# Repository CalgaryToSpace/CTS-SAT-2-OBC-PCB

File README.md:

# CTS-SAT-2-OBC-PCB

This is the design repository for the CTS-SAT-2 onboard computer (OBC) PCB.

This OBC is host to an STM32 and several flash chips, and interfaces with all other electrical components on the 3U CubeSat.

## Repository Contents

* OBC PCB (KiCad; in progress) 
* STM32CubeIDE Pinout/IOC configuration (not yet done)

## Contributors

* Nadeem M ([DeemDeem52](https://github.com/DeemDeem52))
* Others

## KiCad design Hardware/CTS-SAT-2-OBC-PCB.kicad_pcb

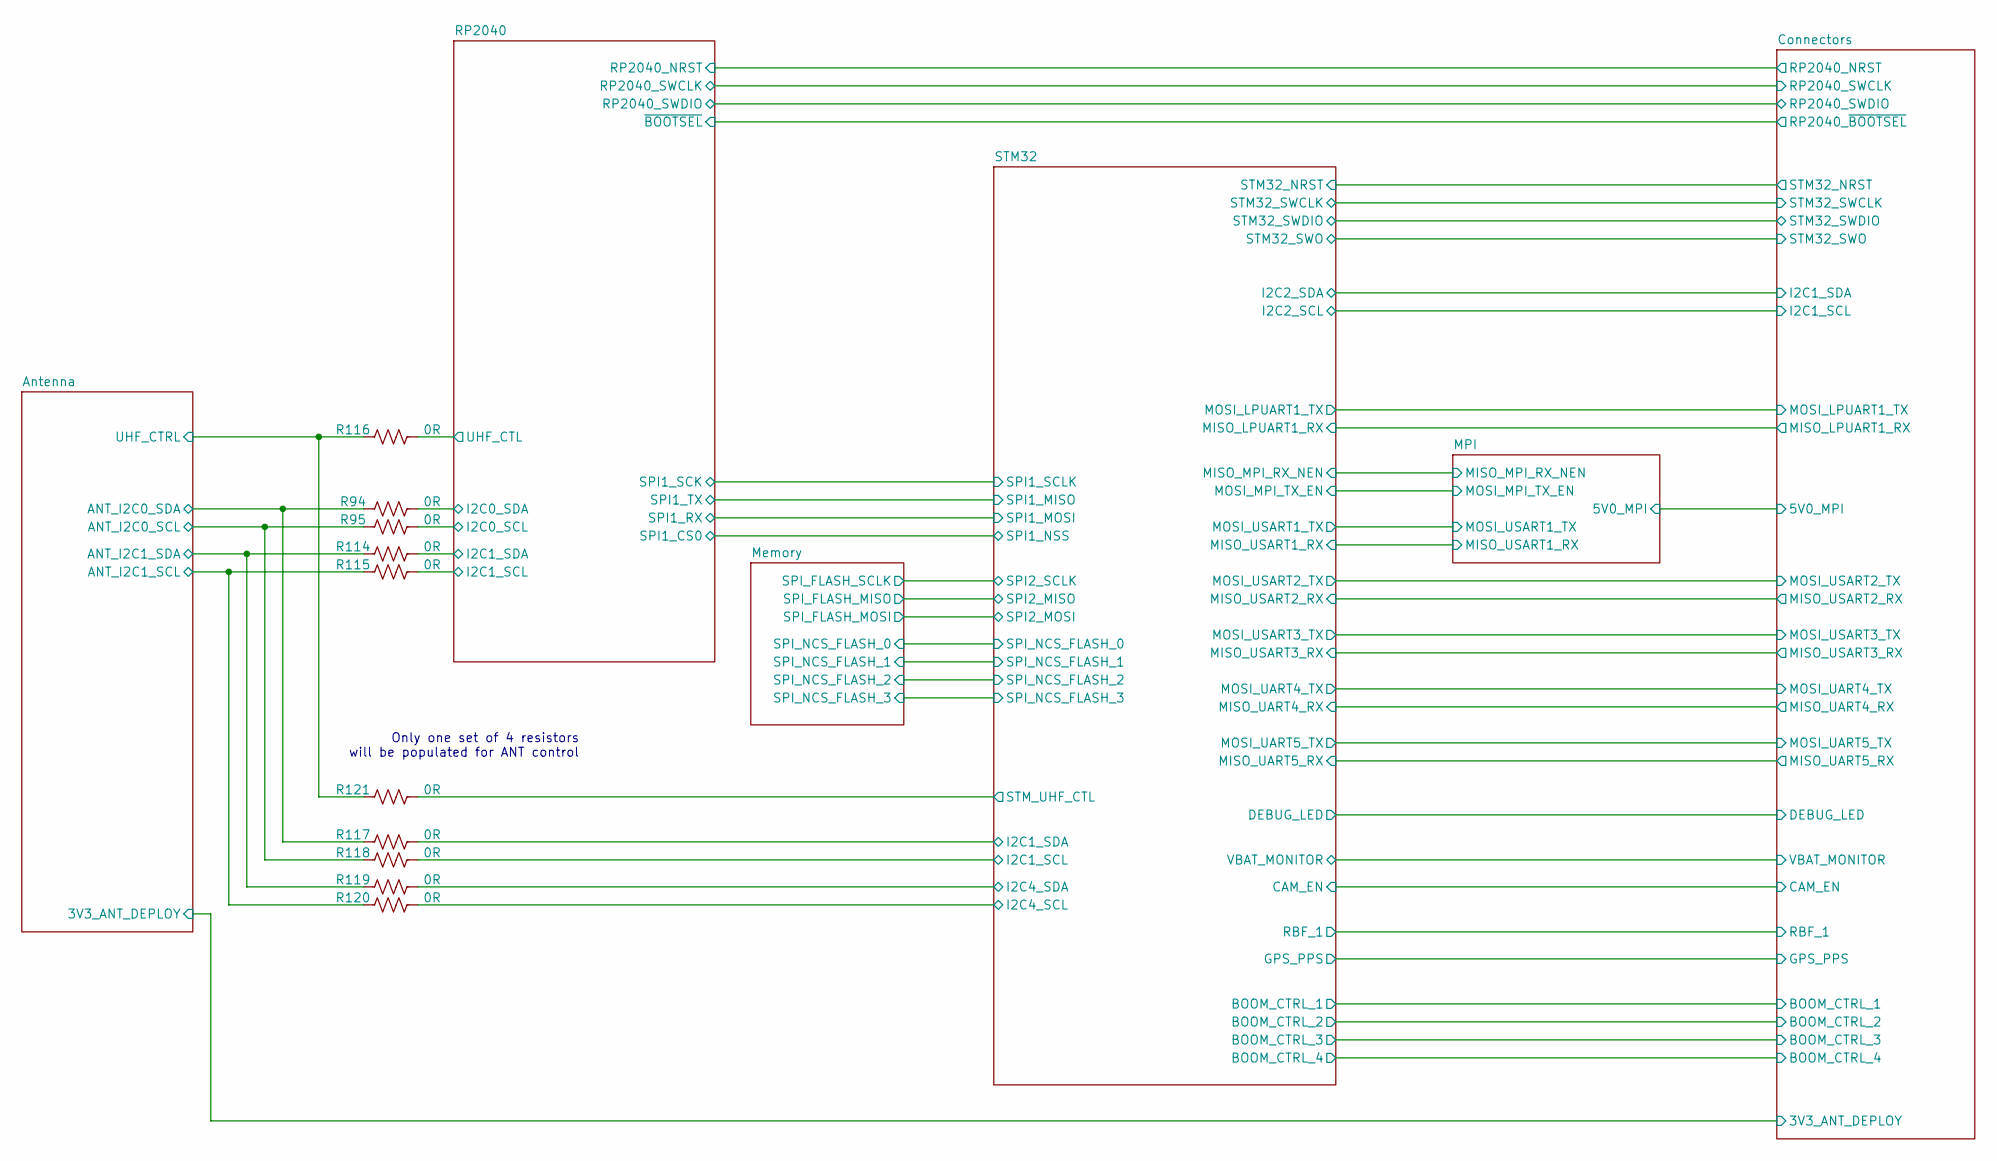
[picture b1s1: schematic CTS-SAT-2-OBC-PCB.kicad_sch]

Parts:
R94, R95, R114, R115, R116, R117, R118, R119, R120, R121: 0R; R_0603_1608Metric

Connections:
/Antenna/ANT_I2C0_SCL: R95.1, R118.1; also elsewhere on the board
/Antenna/ANT_I2C0_SDA: R94.1, R117.1; also elsewhere on the board
/Antenna/ANT_I2C1_SCL: R115.1, R120.1; also elsewhere on the board
/Antenna/ANT_I2C1_SDA: R114.1, R119.1; also elsewhere on the board
/Antenna/UHF_CTRL: R116.1, R121.1; also elsewhere on the board
/RP2040/I2C0_SCL: R95.2; also elsewhere on the board
/RP2040/I2C0_SDA: R94.2; also elsewhere on the board
/RP2040/I2C1_SCL: R115.2; also elsewhere on the board
/RP2040/I2C1_SDA: R114.2; also elsewhere on the board
/RP2040/UHF_CTL: R116.2; also elsewhere on the board
/STM32/I2C1_SCL: R118.2; also elsewhere on the board
/STM32/I2C1_SDA: R117.2; also elsewhere on the board
/STM32/I2C4_SCL: R120.2; also elsewhere on the board
/STM32/I2C4_SDA: R119.2; also elsewhere on the board
/STM32/STM_UHF_CTL: R121.2

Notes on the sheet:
Only one set of 4 resistors will be populated for ANT control

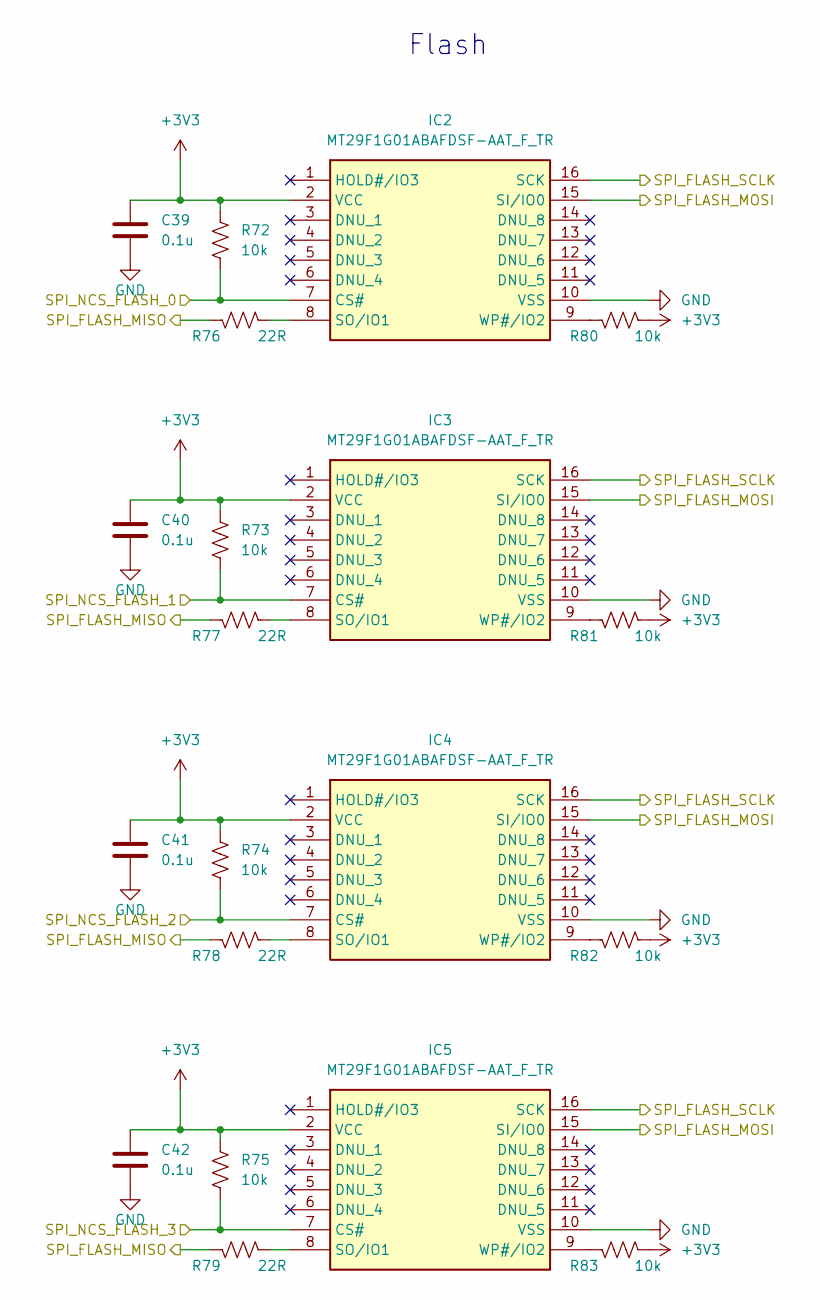
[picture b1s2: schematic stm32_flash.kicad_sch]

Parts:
C39, C40, C41, C42: 0.1u; C_0603_1608Metric
IC2, IC3, IC4, IC5: MT29F1G01ABAFDSF-AAT_F_TR; SOIC-16W_7.5x10.3mm_P1.27mm; Mouser Part Number 340-312330-REEL
R72, R73, R74, R75, R80, R81, R82, R83: 10k; R_0603_1608Metric
R76, R77, R78, R79: 22R; R_0603_1608Metric

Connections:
+3V3: C39.2, C40.2, C41.2, C42.2, IC2.2 (VCC), IC3.2 (VCC), IC4.2 (VCC), IC5.2 (VCC), R72.1, R73.1, R74.1, R75.1, R80.2, R81.2, R82.2, R83.2; also elsewhere on the board
/Memory/SPI_FLASH_MISO: R76.2, R77.2, R78.2, R79.2; also elsewhere on the board
/Memory/SPI_FLASH_MOSI: IC2.15 (SI/IO0), IC3.15 (SI/IO0), IC4.15 (SI/IO0), IC5.15 (SI/IO0); also elsewhere on the board
/Memory/SPI_FLASH_SCLK: IC2.16 (SCK), IC3.16 (SCK), IC4.16 (SCK), IC5.16 (SCK); also elsewhere on the board
/Memory/SPI_NCS_FLASH_0: IC2.7 (CS#), R72.2; also elsewhere on the board
/Memory/SPI_NCS_FLASH_1: IC3.7 (CS#), R73.2; also elsewhere on the board
/Memory/SPI_NCS_FLASH_2: IC4.7 (CS#), R74.2; also elsewhere on the board
/Memory/SPI_NCS_FLASH_3: IC5.7 (CS#), R75.2; also elsewhere on the board
GND: C39.1, C40.1, C41.1, C42.1, IC2.10 (VSS), IC3.10 (VSS), IC4.10 (VSS), IC5.10 (VSS); also elsewhere on the board
unnamed: IC2.8 (SO/IO1), R76.1
unnamed: IC2.9 (WP#/IO2), R80.1
unnamed: IC3.8 (SO/IO1), R77.1
unnamed: IC3.9 (WP#/IO2), R81.1
unnamed: IC4.8 (SO/IO1), R78.1
unnamed: IC4.9 (WP#/IO2), R82.1
unnamed: IC5.8 (SO/IO1), R79.1
unnamed: IC5.9 (WP#/IO2), R83.1

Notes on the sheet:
Flash

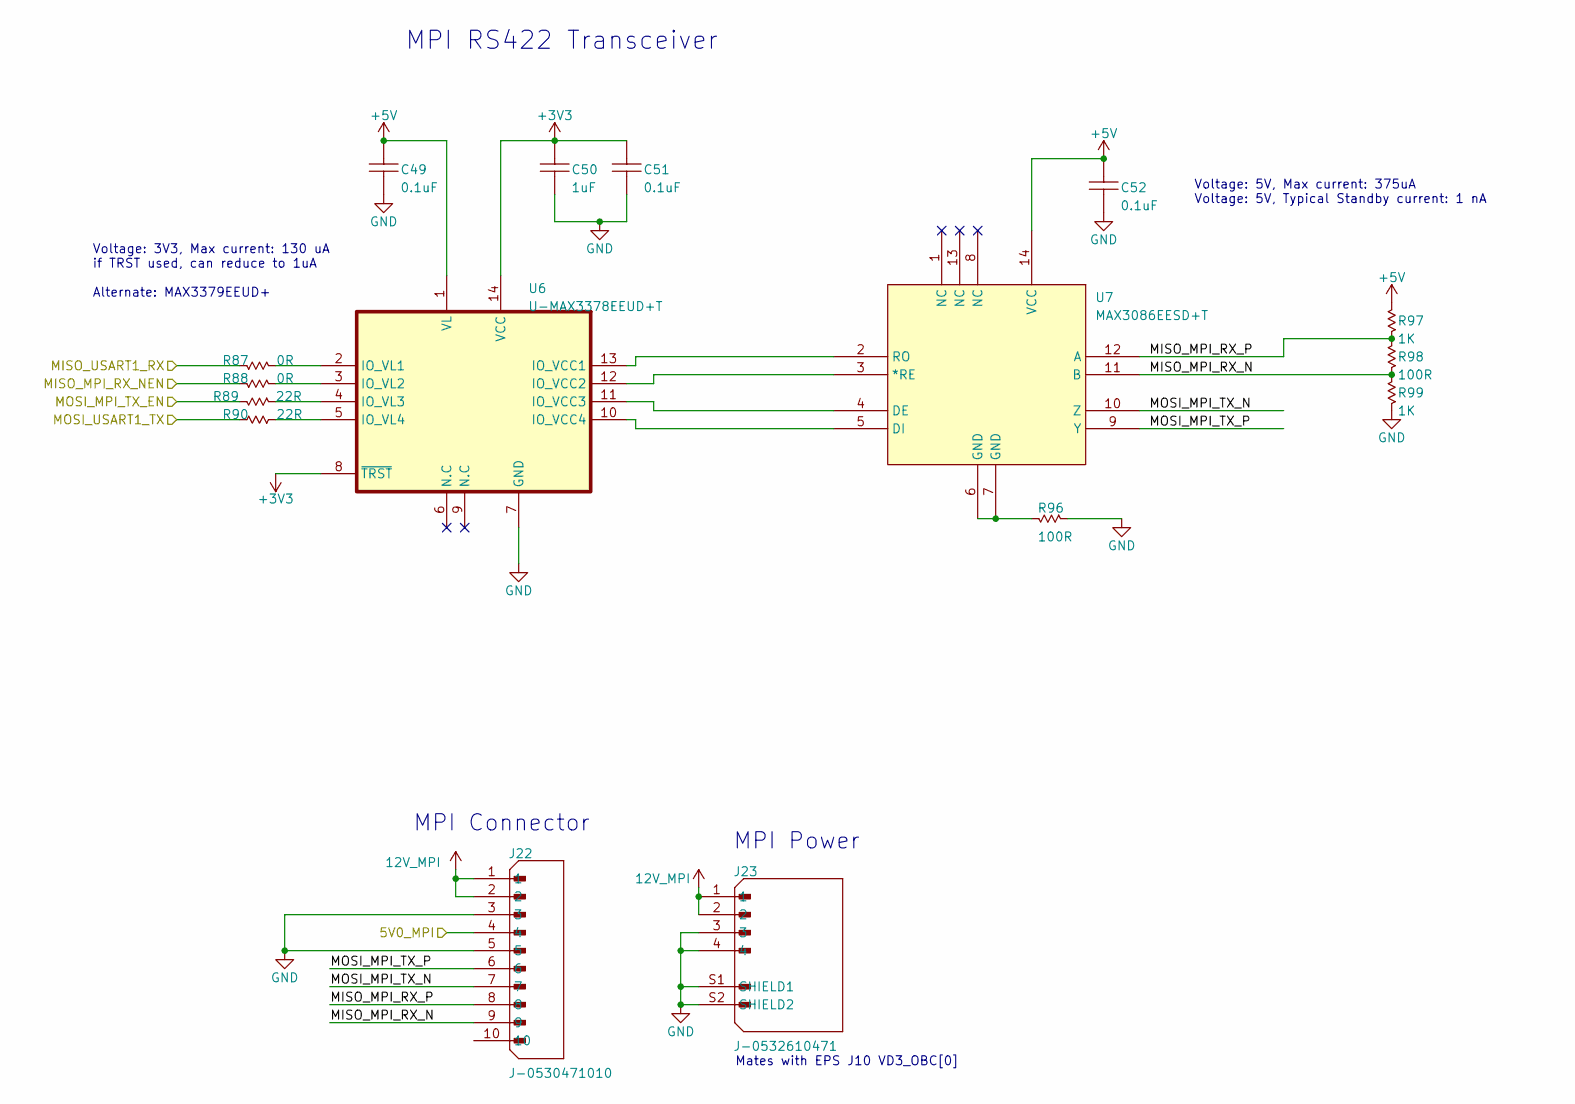
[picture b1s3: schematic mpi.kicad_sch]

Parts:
C49, C51, C52: 0.1uF; C_0603_1608Metric; RATED VOLTAGE 25; MANUFACTURER PART # GCJ188R71E104KA12D
C50: 1uF; C_0603_1608Metric; MANUFACTURER PART # CC0603KRX7R8BB105
J22: J-0530471010; MANUFACTURER PART # 0530471010
J23: J-0532610471; J-53261-0471; MANFACTURER PART # 0532610471
R87, R88: 0R; R_0603_1608Metric; MANUFACTURER PART # RMCF0603ZT0R00
R89, R90: 22R; R_0603_1608Metric; MANUFACTURER PART # RR0816Q-220-D
R96, R98: 100R; R_0603_1608Metric; MANUFACTURER PART # RR08P100DCT-ND
R97, R99: 1K; R_0603_1608Metric; MANUFACTURER PART # CPF0603F1K0C1
U6: U-MAX3378EEUD+T; MANUFACTURER PART # MAX3378EEUD+T; LCSC PART # C143441
U7: MAX3086EESD+T; U-MAX3086EESD+T; MANUFACTURER PART # MAX3086EESD+T; LCSC PART # C2671104

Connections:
12V_MPI: J22.1, J22.2, J23.1, J23.2
+3V3: C50.2, C51.1, U6.8 (~TRST), U6.14 (VCC); also elsewhere on the board
+5V: C49.1, C52.1, R97.2, U6.1 (VL), U7.14 (VCC); also elsewhere on the board
/Connectors/5V0_MPI: J22.4; also elsewhere on the board
/MPI/MISO_MPI_RX_N: J22.9, R98.1, R99.2, U7.11 (B)
/MPI/MISO_MPI_RX_NEN: R88.1; also elsewhere on the board
/MPI/MISO_MPI_RX_P: J22.8, R97.1, R98.2, U7.12 (A)
/MPI/MISO_USART1_RX: R87.1; also elsewhere on the board
/MPI/MOSI_MPI_TX_EN: R89.2; also elsewhere on the board
/MPI/MOSI_MPI_TX_N: J22.7, U7.10 (Z)
/MPI/MOSI_MPI_TX_P: J22.6, U7.9 (Y)
/MPI/MOSI_USART1_TX: R90.2; also elsewhere on the board
GND: C49.2, C50.1, C51.2, C52.2, J22.3, J22.5, J23.3, J23.4, J23.S1 (SHIELD1), J23.S2 (SHIELD2), R96.1, R99.1, U6.7 (GND); also elsewhere on the board
unnamed: R96.2, U7.6 (GND), U7.7 (GND)
unnamed: U6.13 (IO_VCC1), U7.2 (RO)
unnamed: U6.12 (IO_VCC2), U7.3 (*RE)
unnamed: U6.11 (IO_VCC3), U7.4 (DE)
unnamed: U6.10 (IO_VCC4), U7.5 (DI)
unnamed: R87.2, U6.2 (IO_VL1)
unnamed: R88.2, U6.3 (IO_VL2)
unnamed: R89.1, U6.4 (IO_VL3)
unnamed: R90.1, U6.5 (IO_VL4)

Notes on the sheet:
Voltage: 3V3, Max current: 130 uA if TRST used, can reduce to 1uA Alternate: MAX3379EEUD+
Voltage: 5V, Max current: 375uA Voltage: 5V, Typical Standby current: 1 nA
Mates with EPS J10 VD3_OBC[0]
MPI Connector
MPI Power
MPI RS422 Transceiver

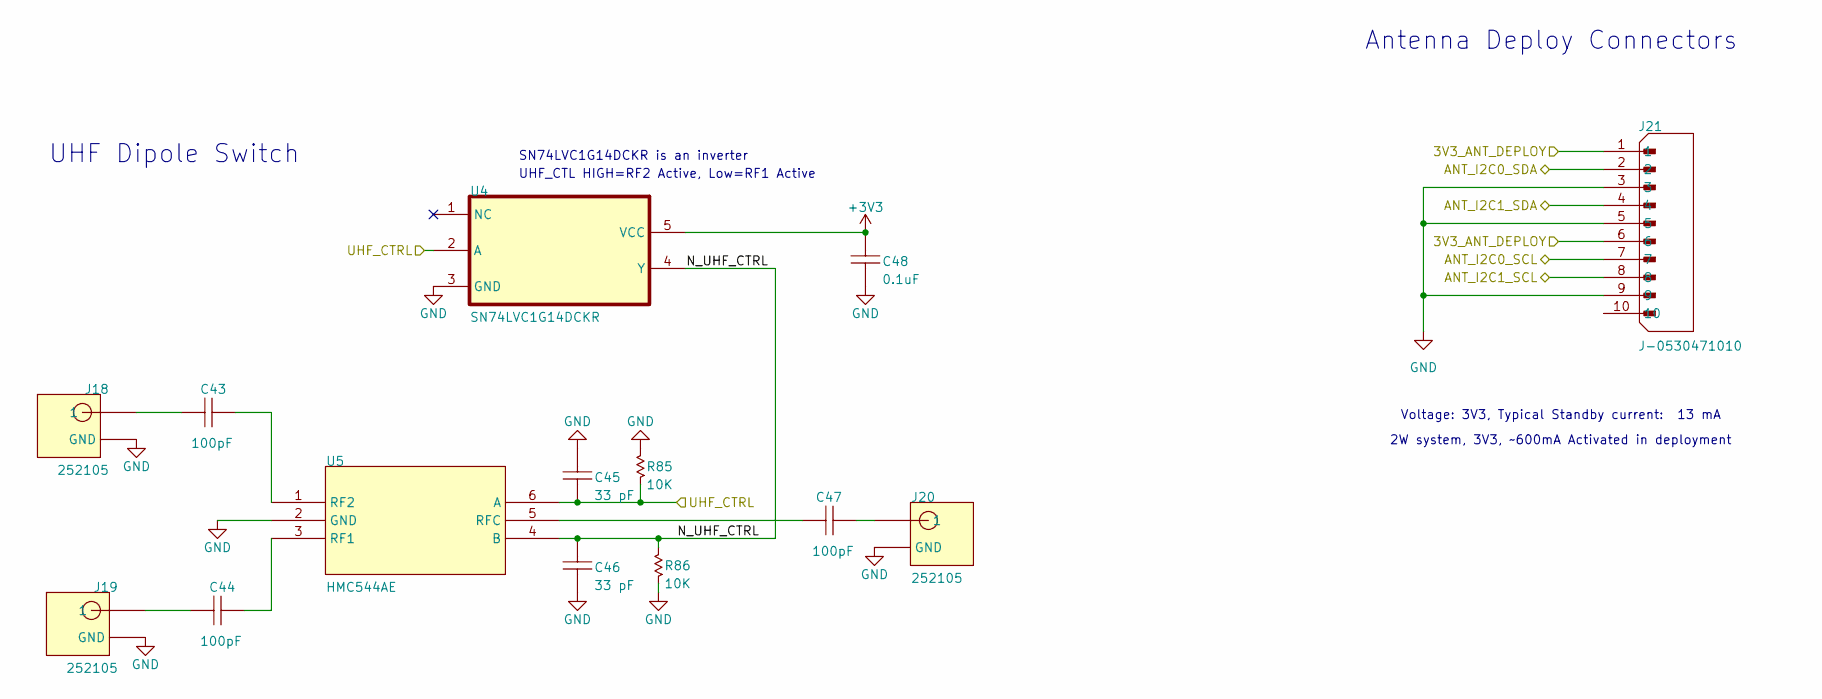
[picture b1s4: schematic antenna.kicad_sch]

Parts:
C43, C44, C47: 100pF; C_0603_1608Metric; MANUFACTURER PART # CC0603KRX7R9BB101
C45, C46: 33 pF; C_0603_1608Metric; MANUFACTURER PART # C0603C330K5RAC7867
C48: 0.1uF; C_0603_1608Metric; RATED VOLTAGE 25; MANUFACTURER PART # GCJ188R71E104KA12D
J18, J19, J20: 252105; J-252105; MANUFACTURER PART # 252105
J21: J-0530471010; MANUFACTURER PART # 0530471010
R85, R86: 10K; R_0603_1608Metric; MANUFACTURER PART # CPF0603B10KE
U4: SN74LVC1G14DCKR; U-SN74LVC1G14DCKR; MANUFACTURER PART # SN74LVC1G14DCKR; LCSC PART # C35740
U5: HMC544AE; U-HMC544AETR; MANUFACTURER PART # HMC544AETR; LCSC PART # C579555

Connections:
+3V3: C48.2, U4.5 (VCC); also elsewhere on the board
/Antenna/3V3_ANT_DEPLOY: J21.1, J21.6; also elsewhere on the board
/Antenna/ANT_I2C0_SCL: J21.7; also elsewhere on the board
/Antenna/ANT_I2C0_SDA: J21.2; also elsewhere on the board
/Antenna/ANT_I2C1_SCL: J21.8; also elsewhere on the board
/Antenna/ANT_I2C1_SDA: J21.4; also elsewhere on the board
/Antenna/N_UHF_CTRL: C46.2, R86.2, U4.4 (Y), U5.4 (B)
/Antenna/UHF_CTRL: C45.1, R85.1, U4.2 (A), U5.6 (A); also elsewhere on the board
GND: C45.2, C46.1, C48.1, J18.0 (GND), J19.0 (GND), J20.0 (GND), J21.3, J21.5, J21.9, R85.2, R86.1, U4.3 (GND), U5.2 (GND); also elsewhere on the board
unnamed: C43.1, J18.1
unnamed: C44.1, J19.1
unnamed: C47.2, J20.1
unnamed: C44.2, U5.3 (RF1)
unnamed: C43.2, U5.1 (RF2)
unnamed: C47.1, U5.5 (RFC)

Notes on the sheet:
Antenna Deploy Connectors
Voltage: 3V3, Typical Standby current: 13 mA
SN74LVC1G14DCKR is an inverter
UHF Dipole Switch
UHF_CTL HIGH=RF2 Active, Low=RF1 Active
2W system, 3V3, ~600mA Activated in deployment

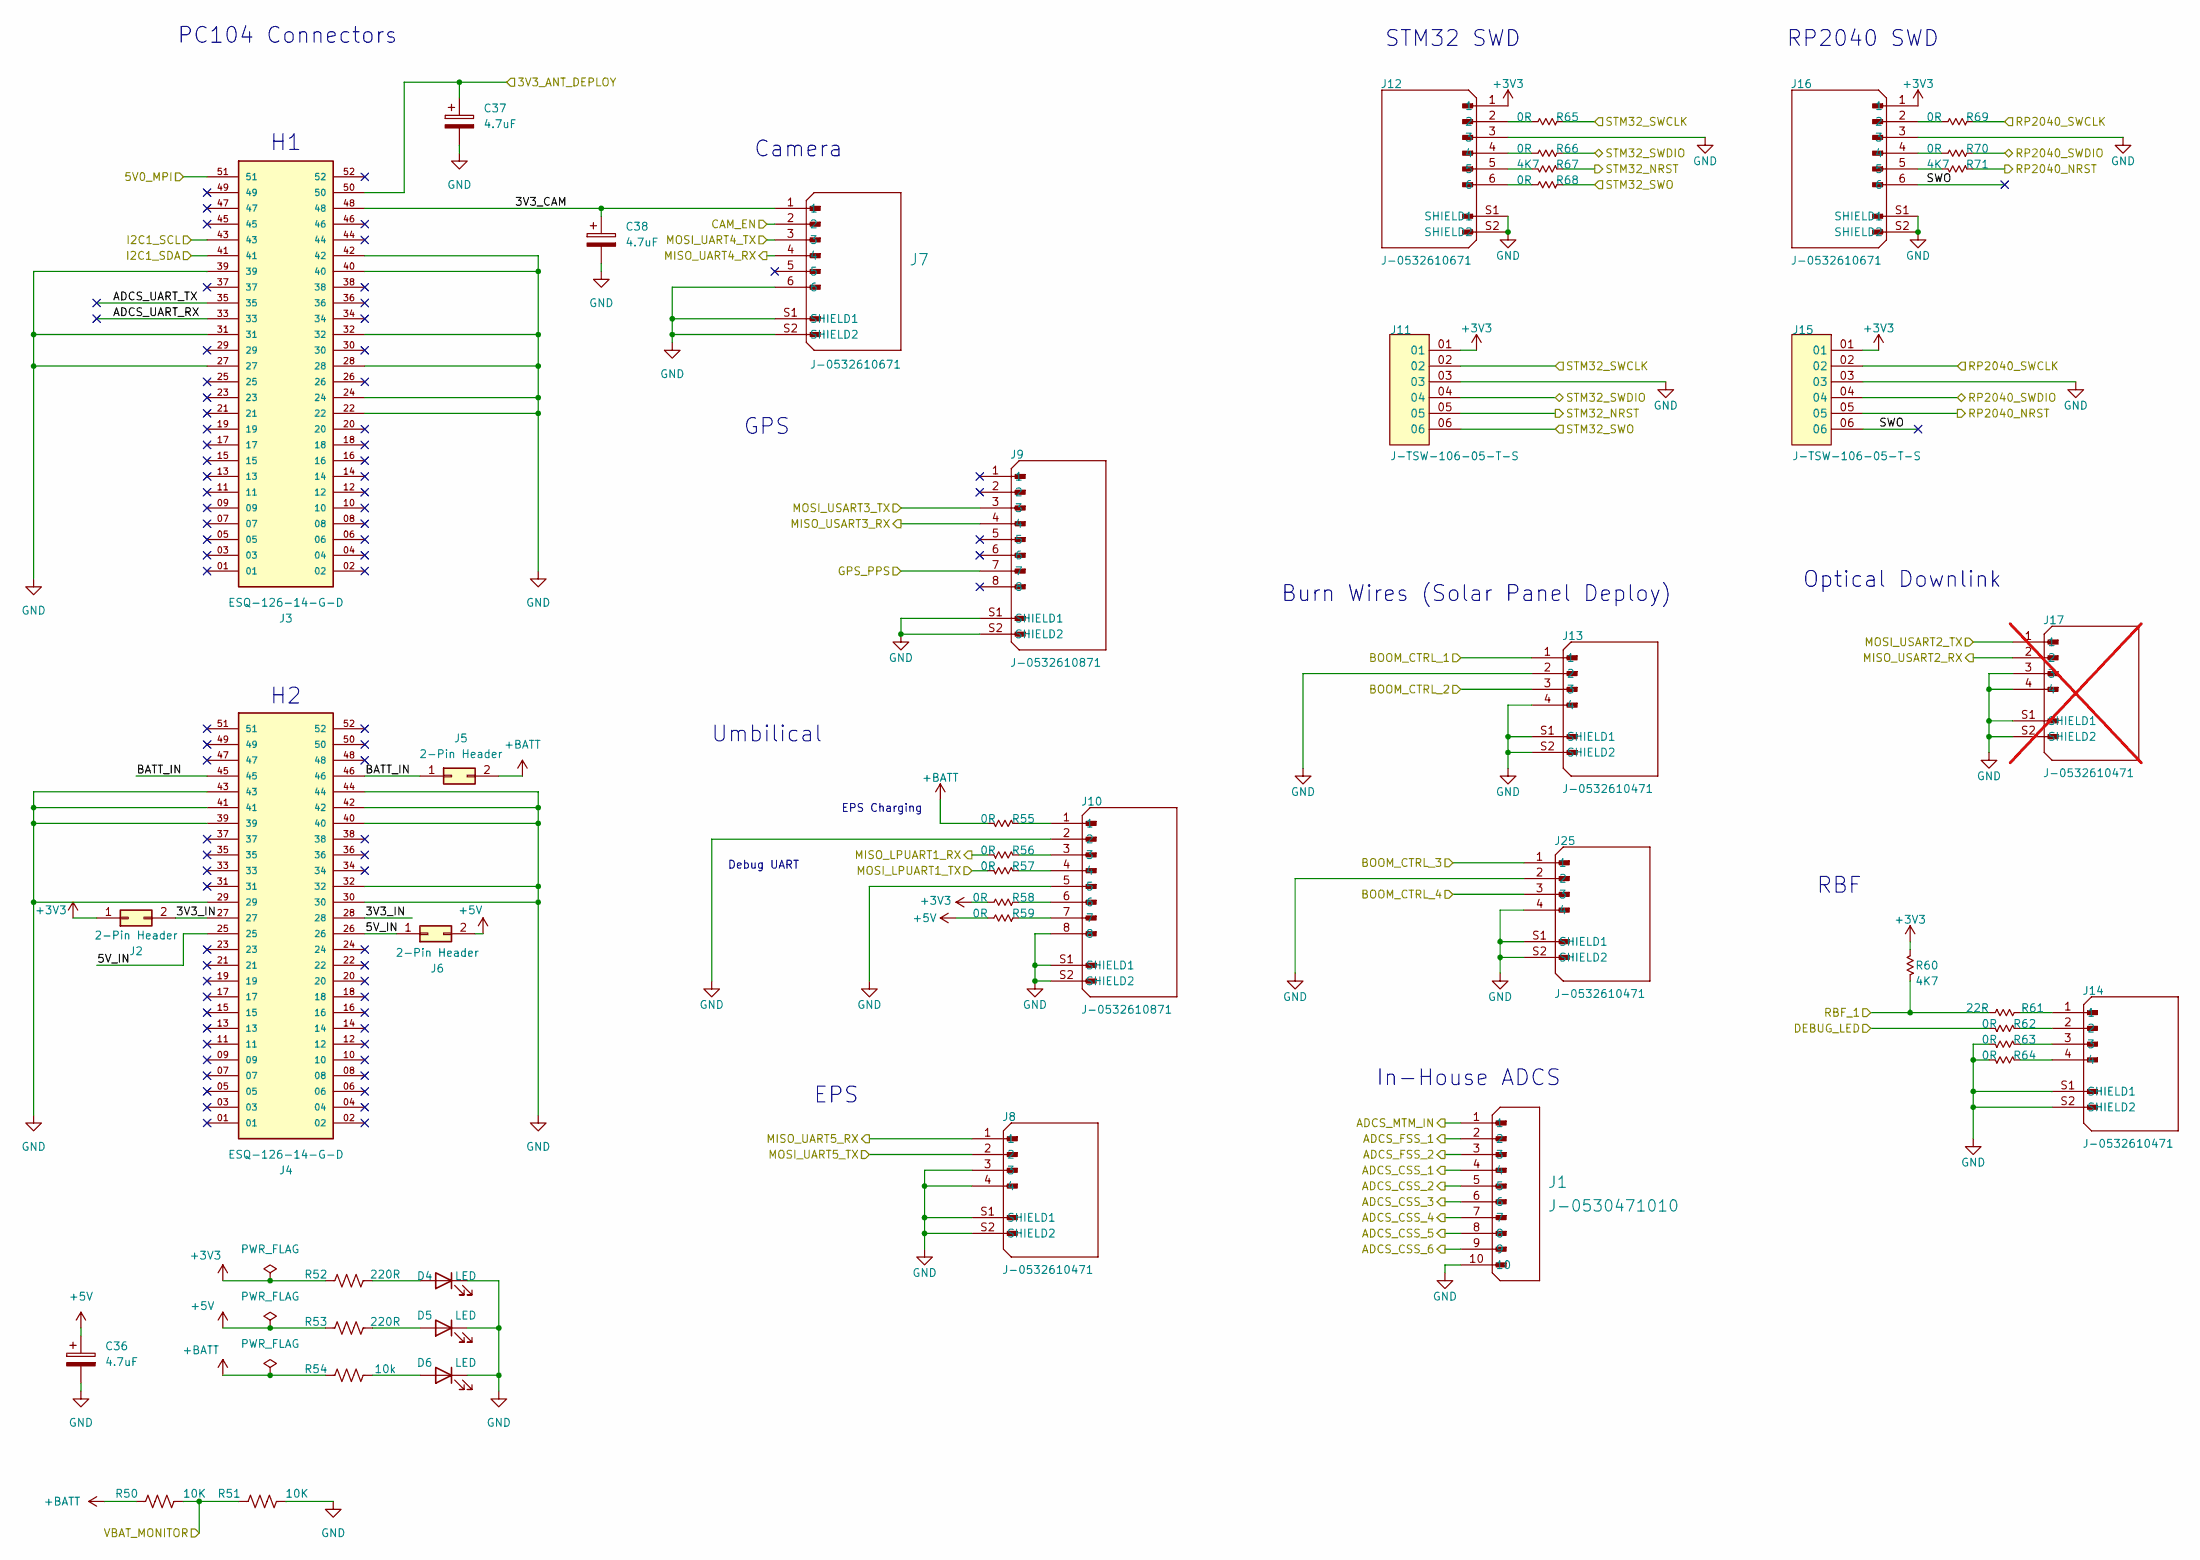
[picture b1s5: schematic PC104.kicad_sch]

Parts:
C36, C37, C38: 4.7uF; C_1206_3216Metric
D4, D5, D6: LED; D-SML-D12U1WT86
J1: J-0530471010; Manufacturer Part # 0530471010
J2, J5, J6: 2-Pin Header; PinHeader_1x02_P1.27mm_Vertical
J3, J4: ESQ-126-14-G-D; SAMTEC_ESQ-126-14-G-D; PARTREV R
J7: J-0532610671; Manfacturer Part # 0532610671
J8, J13, J14, J25: J-0532610471; J-53261-0471; MANFACTURER PART # 0532610471
J9, J10: J-0532610871; J-532610871; MANFACTURER PART # 0532610871
J11, J15: J-TSW-106-05-T-S; MANUFACTURER PART # TSW-106-05-T-S
J12, J16: J-0532610671; MANFACTURER PART # 0532610671
J17: J-0532610471; J-53261-0471; MANFACTURER PART # 0532610471; not fitted
R50, R51: 10K; R_0603_1608Metric
R52, R53: 220R; R_0603_1608Metric
R54: 10k; R_0603_1608Metric
R55, R56, R57, R58, R59, R62, R63, R64, R65, R66, R68, R69, R70: 0R; R_0603_1608Metric; MANUFACTURER PART # RMCF0603ZT0R00
R60, R67, R71: 4K7; R_0603_1608Metric; MANUFACTURER PART # CR0603-FX-4701ELF
R61: 22R; R_0603_1608Metric; MANUFACTURER PART # RR0816Q-220-D

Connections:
+3V3: J2.1, J11.01, J12.1, J15.01, J16.1, R52.1, R58.2, R60.2; also elsewhere on the board
+5V: C36.1, J6.2, R53.1, R59.2; also elsewhere on the board
+BATT: J5.2, R50.1, R54.1, R55.1
/Antenna/3V3_ANT_DEPLOY: C37.1, J3.50; also elsewhere on the board
/Connectors/3V3_CAM: C38.1, J3.48, J7.1
/Connectors/3V3_IN: J2.2, J4.27, J4.28
/Connectors/5V0_MPI: J3.51; also elsewhere on the board
/Connectors/5V_IN: J4.25, J4.26, J6.1
/Connectors/ADCS_CSS_1: J1.4
/Connectors/ADCS_CSS_2: J1.5
/Connectors/ADCS_CSS_3: J1.6
/Connectors/ADCS_CSS_4: J1.7
/Connectors/ADCS_CSS_5: J1.8
/Connectors/ADCS_CSS_6: J1.9
/Connectors/ADCS_FSS_1: J1.2
/Connectors/ADCS_FSS_2: J1.3
/Connectors/ADCS_MTM_IN: J1.1
/Connectors/ADCS_UART_RX: J3.33
/Connectors/ADCS_UART_TX: J3.35
/Connectors/BATT_IN: J4.45, J4.46, J5.1
/Connectors/BOOM_CTRL_1: J13.1; also elsewhere on the board
/Connectors/BOOM_CTRL_2: J13.3; also elsewhere on the board
/Connectors/BOOM_CTRL_3: J25.1; also elsewhere on the board
/Connectors/BOOM_CTRL_4: J25.3; also elsewhere on the board
/Connectors/CAM_EN: J7.2; also elsewhere on the board
/Connectors/DEBUG_LED: R62.1; also elsewhere on the board
/Connectors/GPS_PPS: J9.7; also elsewhere on the board
/Connectors/MISO_LPUART1_RX: R56.1; also elsewhere on the board
/Connectors/MISO_UART4_RX: J7.4; also elsewhere on the board
/Connectors/MISO_UART5_RX: J8.1; also elsewhere on the board
/Connectors/MISO_USART3_RX: J9.4; also elsewhere on the board
/Connectors/MOSI_LPUART1_TX: R57.1; also elsewhere on the board
/Connectors/MOSI_UART4_TX: J7.3; also elsewhere on the board
/Connectors/MOSI_UART5_TX: J8.2; also elsewhere on the board
/Connectors/MOSI_USART3_TX: J9.3; also elsewhere on the board
/Connectors/RBF_1: R60.1, R61.1; also elsewhere on the board
/Connectors/RP2040_NRST: J15.05, R71.1; also elsewhere on the board
/Connectors/RP2040_SWCLK: J15.02, R69.1; also elsewhere on the board
/Connectors/RP2040_SWDIO: J15.04, R70.1; also elsewhere on the board
/Connectors/STM32_NRST: J11.05, R67.1; also elsewhere on the board
/Connectors/STM32_SWCLK: J11.02, R65.1; also elsewhere on the board
/Connectors/STM32_SWDIO: J11.04, R66.1; also elsewhere on the board
/Connectors/STM32_SWO: J11.06, R68.1; also elsewhere on the board
/Connectors/SWO: J15.06, J16.6
/Connectors/VBAT_MONITOR: R50.2, R51.1; also elsewhere on the board
/STM32/I2C2_SCL: J3.43; also elsewhere on the board
/STM32/I2C2_SDA: J3.41; also elsewhere on the board
GND: C36.2, C37.2, C38.2, D4.1 (K), D5.1 (K), D6.1 (K), J1.10, J3.22, J3.24, J3.27, J3.28, J3.31, J3.32, J3.39, J3.40, J3.42, J4.29, J4.30, J4.32, J4.39, J4.40, J4.41, J4.42, J4.43, J4.44, J7.6, J7.S1 (SHIELD1), J7.S2 (SHIELD2), J8.3, J8.4, J8.S1 (SHIELD1), J8.S2 (SHIELD2), J9.S1 (SHIELD1), J9.S2 (SHIELD2), J10.2, J10.5, J10.8, J10.S1 (SHIELD1), J10.S2 (SHIELD2), J11.03, J12.3, J12.S1 (SHIELD1), J12.S2 (SHIELD2), J13.2, J13.4, J13.S1 (SHIELD1), J13.S2 (SHIELD2), J14.S1 (SHIELD1), J14.S2 (SHIELD2), J15.03, J16.3, J16.S1 (SHIELD1), J16.S2 (SHIELD2), J17.3, J17.4, J17.S1 (SHIELD1), J17.S2 (SHIELD2), J25.2, J25.4, J25.S1 (SHIELD1), J25.S2 (SHIELD2), R51.2, R63.1, R64.1; also elsewhere on the board
unnamed: D4.2 (A), R52.2
unnamed: D5.2 (A), R53.2
unnamed: D6.2 (A), R54.2
unnamed: J10.1, R55.2
unnamed: J10.3, R56.2
unnamed: J10.4, R57.2
unnamed: J10.6, R58.1
unnamed: J10.7, R59.1
unnamed: J12.2, R65.2
unnamed: J12.4, R66.2
unnamed: J12.5, R67.2
unnamed: J12.6, R68.2
unnamed: J14.1, R61.2
unnamed: J14.2, R62.2
unnamed: J14.3, R63.2
unnamed: J14.4, R64.2
unnamed: J16.2, R69.2
unnamed: J16.4, R70.2
unnamed: J16.5, R71.2

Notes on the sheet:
PC104 Connectors
RP2040 SWD
RBF
Debug UART
Burn Wires (Solar Panel Deploy)
Optical Downlink
Camera
GPS
EPS
In-House ADCS
Umbilical
EPS Charging
STM32 SWD

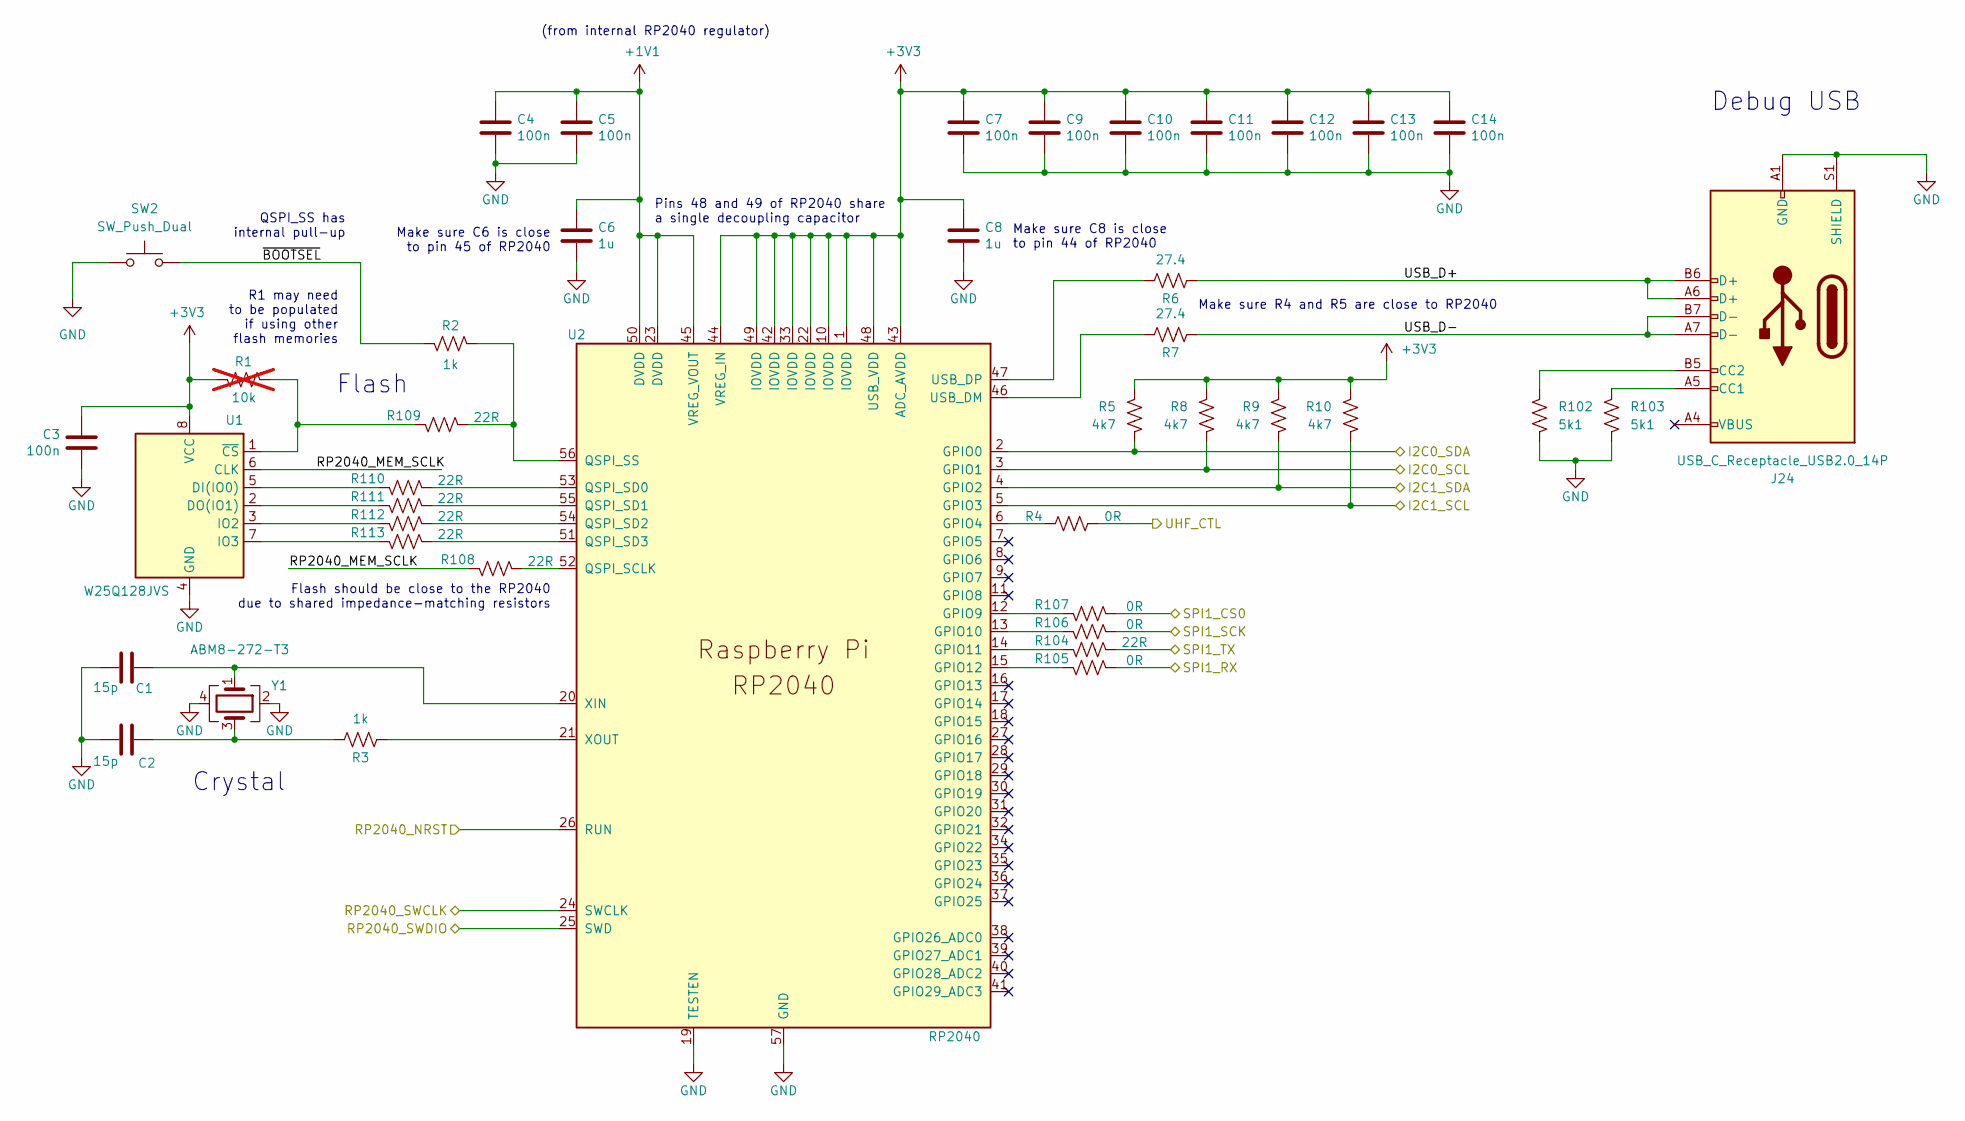
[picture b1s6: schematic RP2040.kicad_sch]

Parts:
C1, C2: 15p; C_0402_1005Metric
C3, C4, C5, C7, C9, C10, C11, C12, C13, C14: 100n; C_0402_1005Metric
C6, C8: 1u; C_0402_1005Metric
J24: USB_C_Receptacle_USB2.0_14P; USB_C_Receptacle_JAE_DX07S024WJ3R400
R1: 10k; R_0402_1005Metric; not fitted
R2, R3: 1k; R_0402_1005Metric
R4, R105, R106, R107: 0R; R_0603_1608Metric
R5, R8, R9, R10: 4k7; R_0603_1608Metric
R6, R7: 27.4; R_0402_1005Metric
R102, R103: 5k1; R_0603_1608Metric
R104, R108, R109, R110, R111, R112, R113: 22R; R_0603_1608Metric
SW2: SW_Push_Dual; SMT_FS
U1: W25Q128JVS; SOIC-8_5.23x5.23mm_P1.27mm
U2: RP2040; RP2040-QFN-56
Y1: ABM8-272-T3; Crystal_SMD_3225-4Pin_3.2x2.5mm

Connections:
+1V1: C4.1, C5.1, C6.1, U2.23 (DVDD), U2.45 (VREG_VOUT), U2.50 (DVDD)
+3V3: C3.1, C7.1, C8.1, C9.1, C10.1, C11.1, C12.1, C13.1, C14.1, R1.2, R5.1, R8.1, R9.1, R10.1, U1.8 (VCC), U2.1 (IOVDD), U2.10 (IOVDD), U2.22 (IOVDD), U2.33 (IOVDD), U2.42 (IOVDD), U2.43 (ADC_AVDD), U2.44 (VREG_IN), U2.48 (USB_VDD), U2.49 (IOVDD); also elsewhere on the board
/Connectors/RP2040_NRST: U2.26 (RUN); also elsewhere on the board
/Connectors/RP2040_SWCLK: U2.24 (SWCLK); also elsewhere on the board
/Connectors/RP2040_SWDIO: U2.25 (SWD); also elsewhere on the board
/RP2040/I2C0_SCL: R8.2, U2.3 (GPIO1); also elsewhere on the board
/RP2040/I2C0_SDA: R5.2, U2.2 (GPIO0); also elsewhere on the board
/RP2040/I2C1_SCL: R10.2, U2.5 (GPIO3); also elsewhere on the board
/RP2040/I2C1_SDA: R9.2, U2.4 (GPIO2); also elsewhere on the board
/RP2040/RP2040_MEM_SCLK: R108.2, U1.6 (CLK)
/RP2040/SPI1_CS0: R107.1; also elsewhere on the board
/RP2040/SPI1_RX: R105.1; also elsewhere on the board
/RP2040/SPI1_SCK: R106.1; also elsewhere on the board
/RP2040/SPI1_TX: R104.1; also elsewhere on the board
/RP2040/UHF_CTL: R4.2; also elsewhere on the board
/RP2040/USB_D+: J24.A6 (D+), J24.B6 (D+), R6.1
/RP2040/USB_D-: J24.A7 (D-), J24.B7 (D-), R7.1
/RP2040/~BOOTSEL: R2.2, SW2.1
GND: C1.2, C2.2, C3.2, C4.2, C5.2, C6.2, C7.2, C8.2, C9.2, C10.2, C11.2, C12.2, C13.2, C14.2, J24.A1 (GND), J24.A12 (GND), J24.B1 (GND), J24.B12 (GND), J24.S1 (SHIELD), R102.2, R103.2, SW2.2, U1.4 (GND), U2.19 (TESTEN), U2.57 (GND), Y1.2, Y1.4; also elsewhere on the board
unnamed: C2.1, R3.2, Y1.3
unnamed: J24.A5 (CC1), R103.1
unnamed: J24.B5 (CC2), R102.1
unnamed: R110.2, U1.5 (DI(IO0))
unnamed: R111.2, U1.2 (DO(IO1))
unnamed: R112.2, U1.3 (IO2)
unnamed: R113.2, U1.7 (IO3)
unnamed: R1.1, R109.2, U1.1 (~CS)
unnamed: R4.1, U2.6 (GPIO4)
unnamed: R107.2, U2.12 (GPIO9)
unnamed: R106.2, U2.13 (GPIO10)
unnamed: R104.2, U2.14 (GPIO11)
unnamed: R105.2, U2.15 (GPIO12)
unnamed: R108.1, U2.52 (QSPI_SCLK)
unnamed: R110.1, U2.53 (QSPI_SD0)
unnamed: R111.1, U2.55 (QSPI_SD1)
unnamed: R112.1, U2.54 (QSPI_SD2)
unnamed: R113.1, U2.51 (QSPI_SD3)
unnamed: R2.1, R109.1, U2.56 (QSPI_SS)
unnamed: R7.2, U2.46 (USB_DM)
unnamed: R6.2, U2.47 (USB_DP)
unnamed: C1.1, U2.20 (XIN), Y1.1
unnamed: R3.1, U2.21 (XOUT)

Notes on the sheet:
Debug USB
Crystal
QSPI_SS has internal pull-up
Pins 48 and 49 of RP2040 share a single decoupling capacitor
Make sure R4 and R5 are close to RP2040
Make sure C6 is close to pin 45 of RP2040
(from internal RP2040 regulator)
R1 may need to be populated if using other flash memories
Flash should be close to the RP2040 due to shared impedance-matching resistors
Flash
Make sure C8 is close to pin 44 of RP2040
